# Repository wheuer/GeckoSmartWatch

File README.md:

# Gecko Smart Watch

This repository tracks the most recent state of my personal smart watch project.

It's a mess and unpolished. For a more in depth look at the project and it's history see [my website](https://www.williamfheuer.com/project-portfolio).

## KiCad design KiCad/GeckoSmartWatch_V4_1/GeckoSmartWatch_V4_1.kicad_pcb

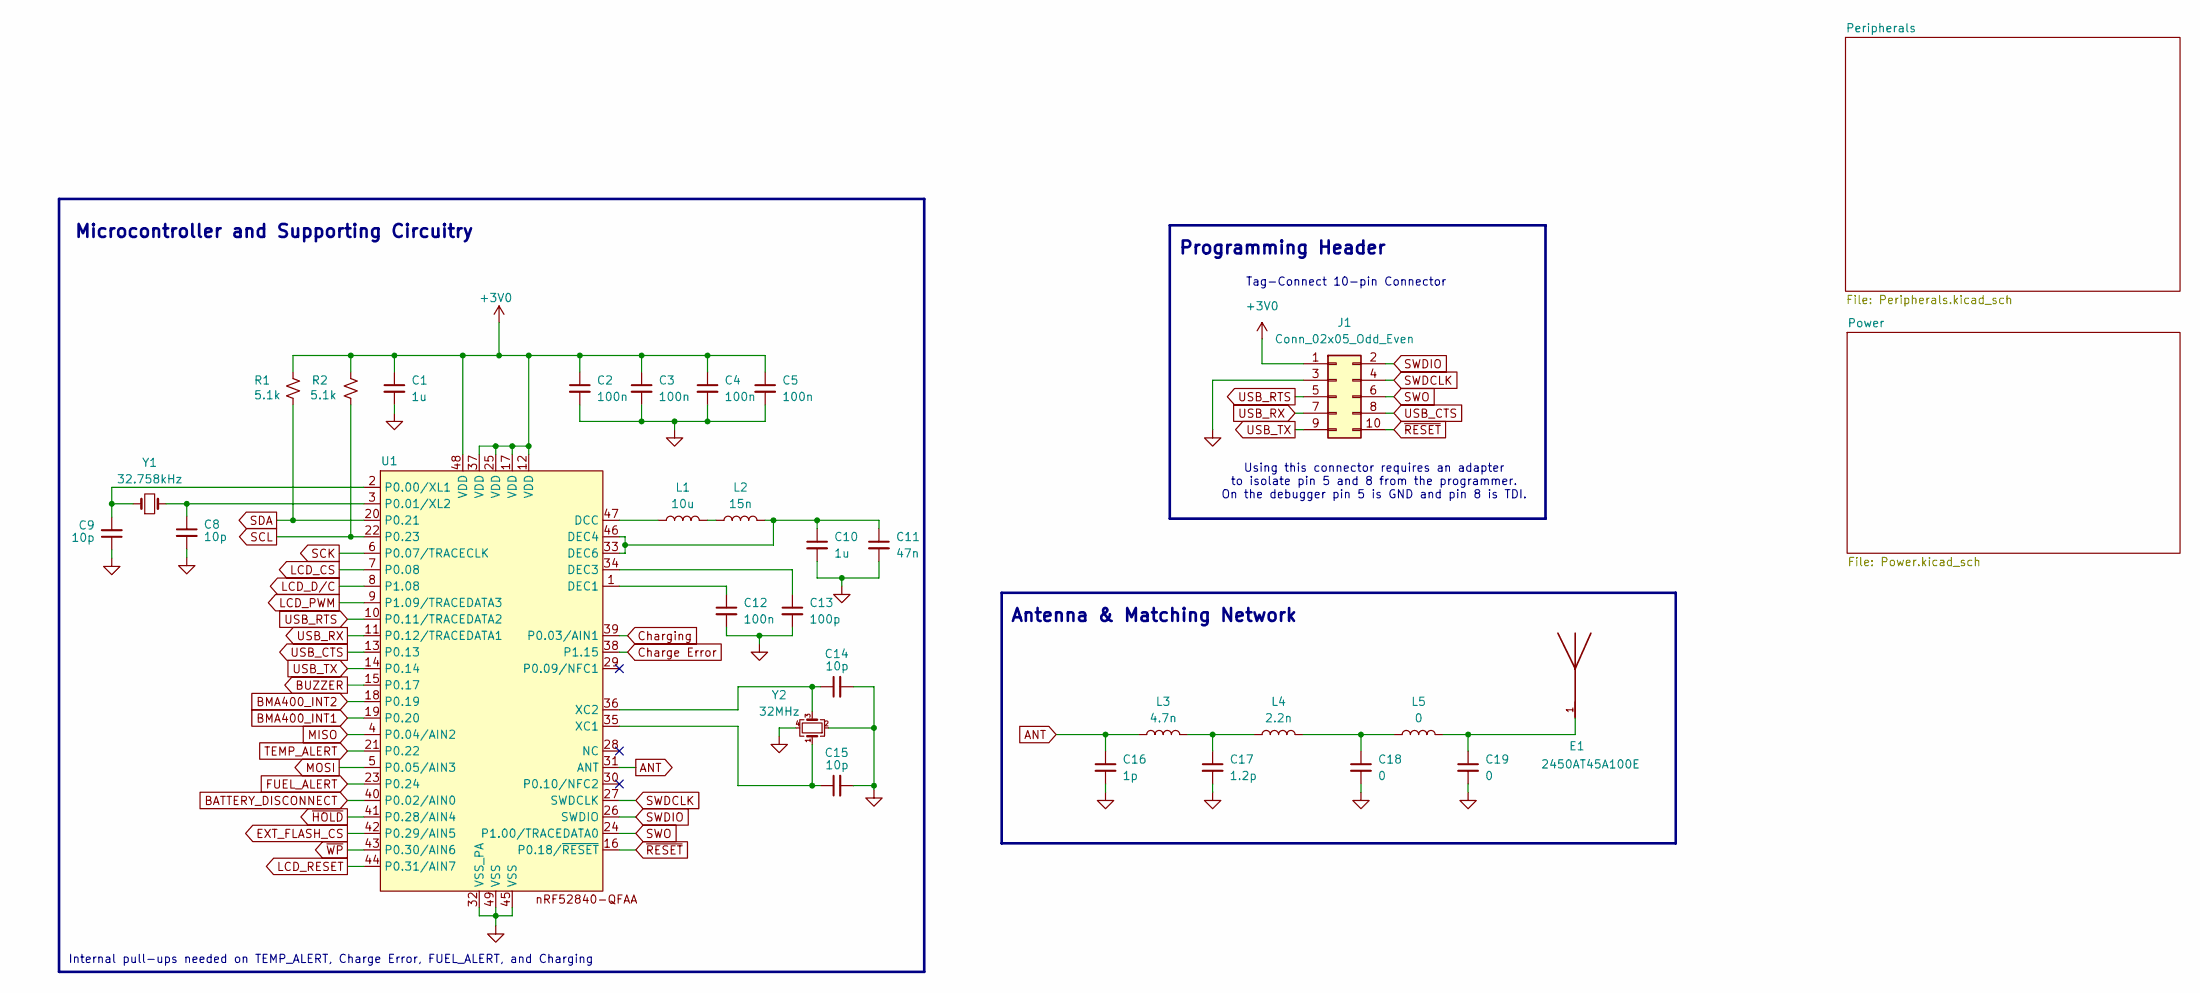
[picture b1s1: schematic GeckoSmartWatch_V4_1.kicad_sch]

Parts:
C1, C10: 1u; C_0402_1005Metric
C2, C3, C4, C5, C12: 100n; C_0402_1005Metric
C8, C9, C14, C15: 10p; C_0402_1005Metric
C11: 47n; C_0402_1005Metric
C13: 100p; C_0402_1005Metric
C16: 1p; C_0402_1005Metric
C17: 1.2p; C_0402_1005Metric
C18, C19: 0; C_0402_1005Metric
E1: 2450AT45A100E; ANT_2450AT45A100E; PARTREV 3.1
J1: Conn_02x05_Odd_Even; TAG-CONNECT_TC2050-IDC-NL
L1: 10u; L_0603_1608Metric
L2: 15n; L_0402_1005Metric
L3: 4.7n; L_0402_1005Metric
L4: 2.2n; L_0402_1005Metric
L5: 0; L_0402_1005Metric
R1, R2: 5.1k; R_0402_1005Metric
U1: nrf52840_QFN40P600X600X95-49N-D
Y1: 32.758kHz; 32kHz_ECS32712512RCTR
Y2: 32MHz; 32MHz_ECS320837CKMTR3

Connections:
+3V0: C1.1, C2.1, C3.1, C4.1, C5.1, J1.1, R1.2, R2.2, U1.12 (VDD), U1.17 (VDD), U1.25 (VDD), U1.37 (VDD), U1.48 (VDD); also elsewhere on the board
ANT: C16.1, L3.1, U1.31 (ANT)
BATTERY_DISCONNECT: U1.40 (P0.02/AIN0); also elsewhere on the board
BMA400_INT1: U1.19 (P0.20); also elsewhere on the board
BMA400_INT2: U1.18 (P0.19); also elsewhere on the board
BUZZER: U1.15 (P0.17); also elsewhere on the board
Charge Error: U1.38 (P1.15); also elsewhere on the board
Charging: U1.39 (P0.03/AIN1); also elsewhere on the board
EXT_FLASH_CS: U1.42 (P0.29/AIN5); also elsewhere on the board
FUEL_ALERT: U1.23 (P0.24); also elsewhere on the board
GND: C1.2, C2.2, C3.2, C4.2, C5.2, C8.2, C9.1, C10.2, C11.2, C12.2, C13.2, C14.2, C15.2, C16.2, C17.2, C18.2, C19.2, J1.3, U1.32 (VSS_PA), U1.45 (VSS), U1.49 (VSS), Y2.2, Y2.4; also elsewhere on the board
LCD_CS: U1.7 (P0.08); also elsewhere on the board
LCD_D/C: U1.8 (P1.08); also elsewhere on the board
LCD_PWM: U1.9 (P1.09/TRACEDATA3); also elsewhere on the board
LCD_RESET: U1.44 (P0.31/AIN7); also elsewhere on the board
MISO: U1.4 (P0.04/AIN2); also elsewhere on the board
MOSI: U1.5 (P0.05/AIN3); also elsewhere on the board
unnamed: C17.1, L3.2, L4.1
unnamed: C18.1, L4.2, L5.1
unnamed: C19.1, E1.1, L5.2
unnamed: L1.2, L2.1
unnamed: L1.1, U1.47 (DCC)
unnamed: C12.1, U1.1 (DEC1)
unnamed: C13.1, U1.34 (DEC3)
unnamed: C10.1, C11.1, L2.2, U1.33 (DEC6), U1.46 (DEC4)
unnamed: C9.2, U1.2 (P0.00/XL1), Y1.1
unnamed: C8.1, U1.3 (P0.01/XL2), Y1.2
unnamed: C15.1, U1.35 (XC1), Y2.1
unnamed: C14.1, U1.36 (XC2), Y2.3
SCK: U1.6 (P0.07/TRACECLK); also elsewhere on the board
SCL: R2.1, U1.22 (P0.23); also elsewhere on the board
SDA: R1.1, U1.20 (P0.21); also elsewhere on the board
SWDCLK: J1.4, U1.27 (SWDCLK)
SWDIO: J1.2, U1.26 (SWDIO)
SWO: J1.6, U1.24 (P1.00/TRACEDATA0)
TEMP_ALERT: U1.21 (P0.22); also elsewhere on the board
USB_CTS: J1.8, U1.13 (P0.13)
USB_RTS: J1.5, U1.10 (P0.11/TRACEDATA2)
USB_RX: J1.7, U1.11 (P0.12/TRACEDATA1)
USB_TX: J1.9, U1.14 (P0.14)
~HOLD: U1.41 (P0.28/AIN4); also elsewhere on the board
~RESET: J1.10, U1.16 (P0.18/~RESET)
~WP: U1.43 (P0.30/AIN6); also elsewhere on the board

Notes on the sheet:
Antenna & Matching Network
Using this connector requires an adapter to isolate pin 5 and 8 from the programmer. On the debugger pin 5 is GND and pin 8 is TDI.
Internal pull-ups needed on TEMP_ALERT, Charge Error, FUEL_ALERT, and Charging
Tag-Connect 10-pin Connector
Programming Header
Microcontroller and Supporting Circuitry

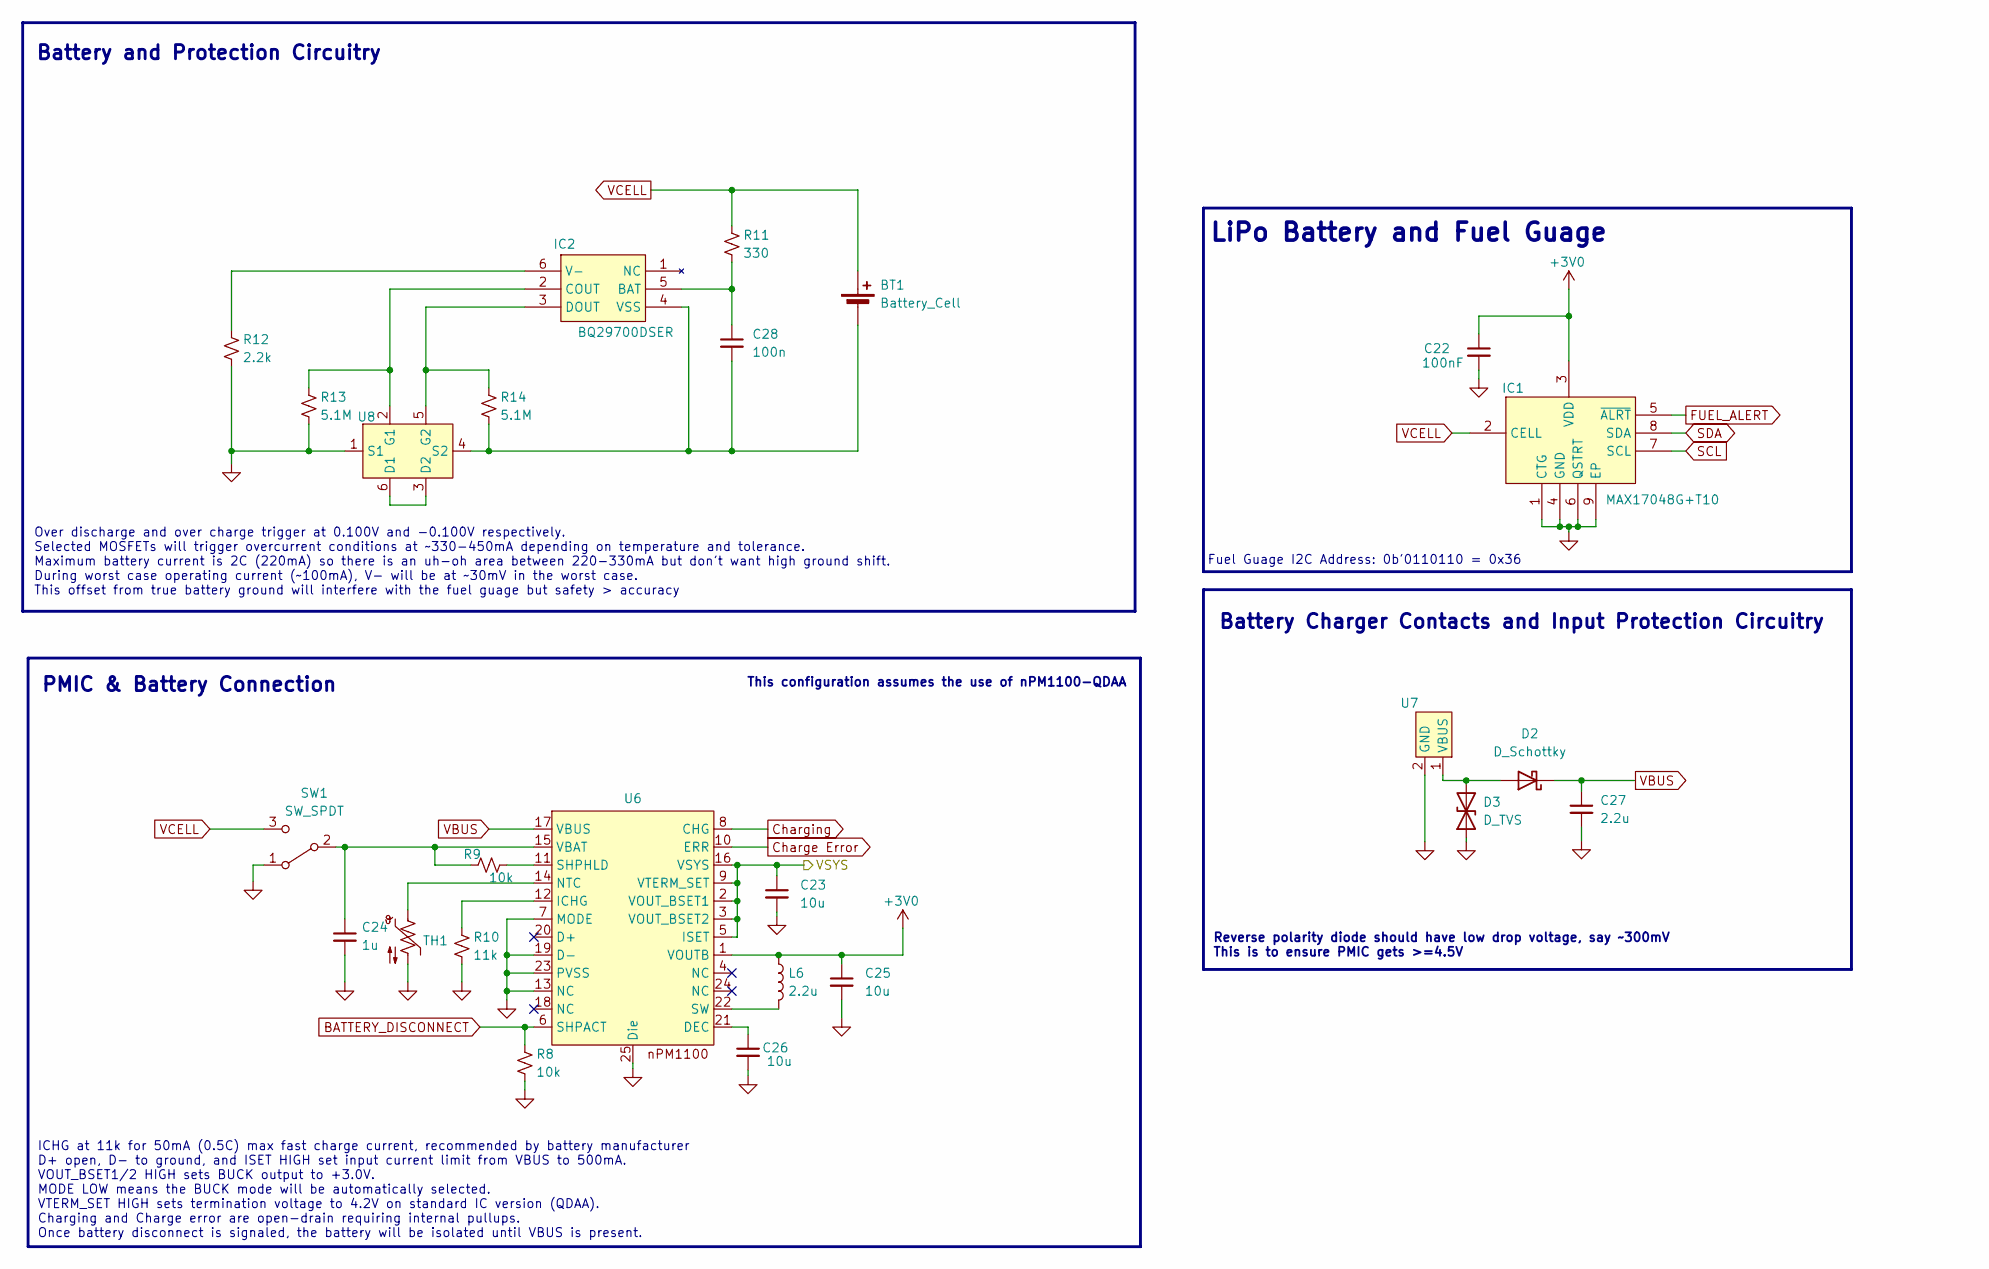
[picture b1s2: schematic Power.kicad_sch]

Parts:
BT1: Battery_Cell; RJD2430C1ST1
C22: 100nF; C_0402_1005Metric
C23, C25, C26: 10u; C_0402_1005Metric
C24: 1u; C_0402_1005Metric
C27: 2.2u; C_0402_1005Metric
C28: 100n; C_0402_1005Metric
D2: D_Schottky; reversePolarity_SODFL3616X98N
D3: D_TVS; TVS_SOD2513X120N
IC1: MAX17048G+T10; MAX17048_fuelGuague; Mouser Part Number 700-MAX17048G+T10
IC2: BQ29700DSER; batProtect_SON50P150X150X80-6N; Mouser Part Number 595-BQ29700DSER
L6: 2.2u; L_0402_1005Metric
R8, R9: 10k; R_0402_1005Metric
R10: 11k; R_0402_1005Metric
R11: 330; R_0402_1005Metric
R12: 2.2k; R_0402_1005Metric
R13, R14: 5.1M; R_0402_1005Metric
SW1: SW_SPDT; pwrSW_B-TYPE
TH1: Thermistor_NTC_US; R_0402_1005Metric
U6: nPM1100_QFN50P400X400X90-25N-D
U7: chargeContacts_RHDR2W51P0X254_1X2_508X254X419P
U8: batMOS_SOTFL95P280X88-6N

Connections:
+3V0: C22.1, C25.1, IC1.3 (VDD), L6.1, U6.1 (VOUTB); also elsewhere on the board
/Power/VSYS: C23.1, U6.2 (VOUT_BSET1), U6.3 (VOUT_BSET2), U6.5 (ISET), U6.9 (VTERM_SET), U6.16 (VSYS)
BATTERY_DISCONNECT: R8.1, U6.6 (SHPACT); also elsewhere on the board
Charge Error: U6.10 (ERR); also elsewhere on the board
Charging: U6.8 (CHG); also elsewhere on the board
FUEL_ALERT: IC1.5 (~ALRT); also elsewhere on the board
GND: C22.2, C23.2, C24.2, C25.2, C26.2, C27.2, D3.1 (A1), IC1.1 (CTG), IC1.4 (GND), IC1.6 (QSTRT), IC1.9 (EP), R8.2, R10.2, R12.2, R13.2, SW1.1 (A), TH1.2, U6.7 (MODE), U6.13 (NC), U6.19 (D-), U6.23 (PVSS), U6.25 (Die), U7.2 (GND), U8.1 (S1); also elsewhere on the board
unnamed: BT1.2 (-), C28.2, IC2.4 (VSS), R14.2, U8.4 (S2)
unnamed: D2.2 (A), D3.2 (A2), U7.1 (VBUS)
unnamed: C28.1, IC2.5 (BAT), R11.2
unnamed: IC2.2 (COUT), R13.1, U8.2 (G1)
unnamed: IC2.3 (DOUT), R14.1, U8.5 (G2)
unnamed: IC2.6 (V-), R12.1
unnamed: C24.1, R9.1, SW1.2 (B), U6.15 (VBAT)
unnamed: C26.1, U6.21 (DEC)
unnamed: R10.1, U6.12 (ICHG)
unnamed: TH1.1, U6.14 (NTC)
unnamed: R9.2, U6.11 (SHPHLD)
unnamed: L6.2, U6.22 (SW)
unnamed: U8.3 (D2), U8.6 (D1)
SCL: IC1.7 (SCL); also elsewhere on the board
SDA: IC1.8 (SDA); also elsewhere on the board
VBUS: C27.1, D2.1 (K), U6.17 (VBUS)
VCELL: BT1.1 (+), IC1.2 (CELL), R11.1, SW1.3 (C)

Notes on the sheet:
Battery and Protection Circuitry
Reverse polarity diode should have low drop voltage, say ~300mV This is to ensure PMIC gets >=4.5V
Over discharge and over charge trigger at 0.100V and -0.100V respectively. Selected MOSFETs will trigger overcurrent conditions at ~330-450mA depending on temperature and tolerance. Maximum battery current is 2C (220mA) so there is an uh-oh area between 220-330mA but don't want high ground shift. D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
This configuration assumes the use of nPM1100-QDAA
Battery Charger Contacts and Input Protection Circuitry
LiPo Battery and Fuel Guage
Fuel Guage I2C Address: 0b'0110110 = 0x36
PMIC & Battery Connection
ICHG at 11k for 50mA (0.5C) max fast charge current, recommended by battery manufacturer D+ open, D- to ground, and ISET HIGH set input current limit from VBUS to 500mA. VOUT_BSET1/2 HIGH sets BUCK output to +3.0V. MODE LOW means the BUCK mode will be automatically selected. VTERM_SET HIGH sets ter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

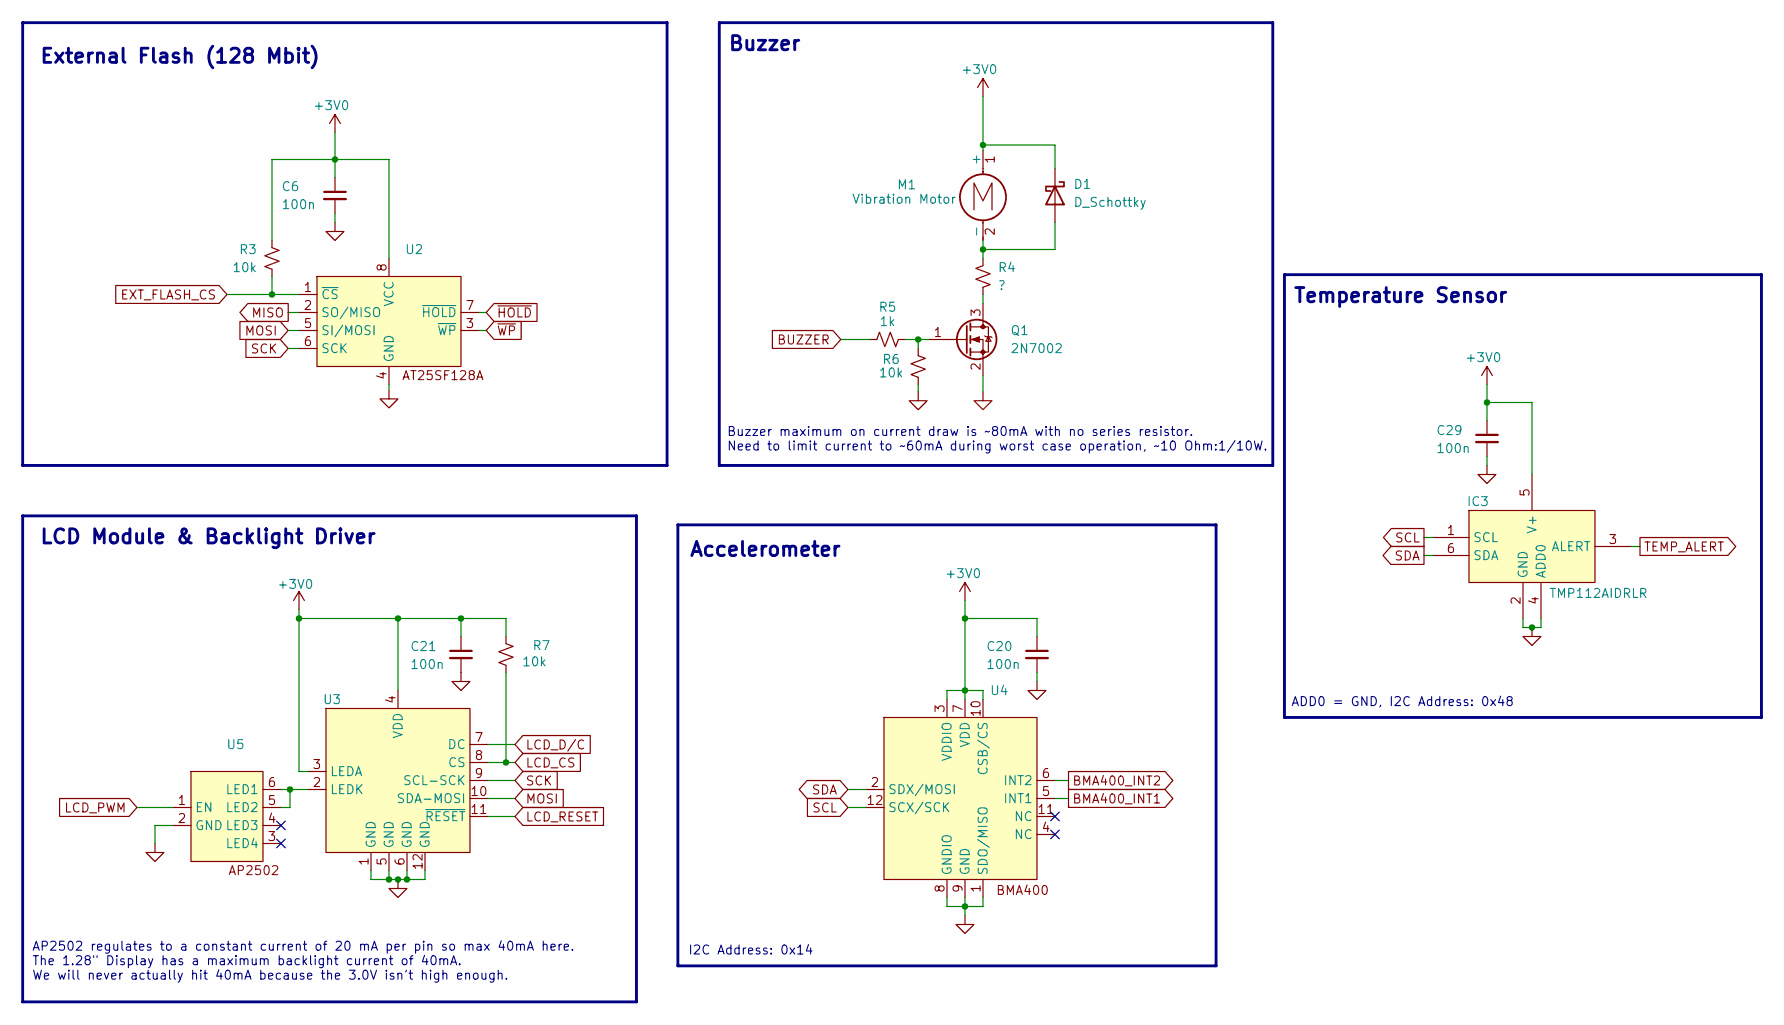
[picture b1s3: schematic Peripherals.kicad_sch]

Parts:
C6, C20, C21, C29: 100n; C_0402_1005Metric
D1: D_Schottky; flyback_SODFL1608X70N
IC3: TMP112AIDRLR; tmp_SOTFL50P160X60-6N; Mouser Part Number 595-TMP112AIDRLR
M1: Vibration Motor; SMD_vibrationMotor
Q1: 2N7002; SOT-23
R3, R6, R7: 10k; R_0402_1005Metric
R4: ?; R_0402_1005Metric
R5: 1k; R_0402_1005Metric
U2: extFlash_SON127P600X500X60-9N-D
U3: 1.47_TFT_displayConnector
U4: BOSCH_LGA_12
U5: AP2502_SOT95P280X145-6N

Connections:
+3V0: C6.1, C20.1, C21.1, C29.1, D1.1 (K), IC3.5 (V+), M1.1 (+), R3.1, R7.1, U2.8 (VCC), U3.3 (LEDA), U3.4 (VDD), U4.3 (VDDIO), U4.7 (VDD), U4.10 (CSB/CS); also elsewhere on the board
BMA400_INT1: U4.5 (INT1); also elsewhere on the board
BMA400_INT2: U4.6 (INT2); also elsewhere on the board
BUZZER: R5.1; also elsewhere on the board
EXT_FLASH_CS: R3.2, U2.1 (~CS); also elsewhere on the board
GND: C6.2, C20.2, C21.2, C29.2, IC3.2 (GND), IC3.4 (ADD0), Q1.2 (S), R6.1, U2.4 (GND), U3.1 (GND), U3.5 (GND), U3.6 (GND), U3.12 (GND), U4.1 (SDO/MISO), U4.8 (GNDIO), U4.9 (GND), U5.2 (GND); also elsewhere on the board
LCD_CS: R7.2, U3.8 (CS); also elsewhere on the board
LCD_D/C: U3.7 (DC); also elsewhere on the board
LCD_PWM: U5.1 (EN); also elsewhere on the board
LCD_RESET: U3.11 (~RESET); also elsewhere on the board
MISO: U2.2 (SO/MISO); also elsewhere on the board
MOSI: U2.5 (SI/MOSI), U3.10 (SDA-MOSI); also elsewhere on the board
unnamed: D1.2 (A), M1.2 (-), R4.1
unnamed: Q1.3 (D), R4.2
unnamed: Q1.1 (G), R5.2, R6.2
unnamed: U3.2 (LEDK), U5.5 (LED2), U5.6 (LED1)
SCK: U2.6 (SCK), U3.9 (SCL-SCK); also elsewhere on the board
SCL: IC3.1 (SCL), U4.12 (SCX/SCK); also elsewhere on the board
SDA: IC3.6 (SDA), U4.2 (SDX/MOSI); also elsewhere on the board
TEMP_ALERT: IC3.3 (ALERT); also elsewhere on the board
~HOLD: U2.7 (~HOLD); also elsewhere on the board
~WP: U2.3 (~WP); also elsewhere on the board

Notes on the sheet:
Buzzer
I2C Address: 0x14
ADD0 = GND, I2C Address: 0x48
AP2502 regulates to a constant current of 20 mA per pin so max 40mA here. The 1.28" Display has a maximum backlight current of 40mA. We will never actually hit 40mA because the 3.0V isn't high enough.
Buzzer maximum on current draw is ~80mA with no series resistor. Need to limit current to ~60mA during worst case operation, ~10 Ohm:1/10W.
Temperature Sensor
External Flash (128 Mbit)
LCD Module & Backlight Driver
Accelerometer

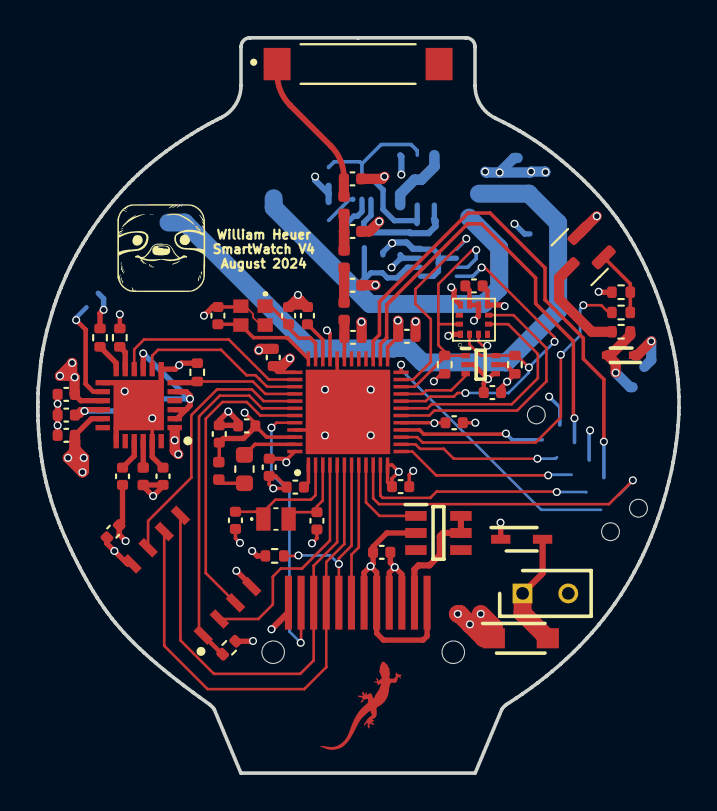
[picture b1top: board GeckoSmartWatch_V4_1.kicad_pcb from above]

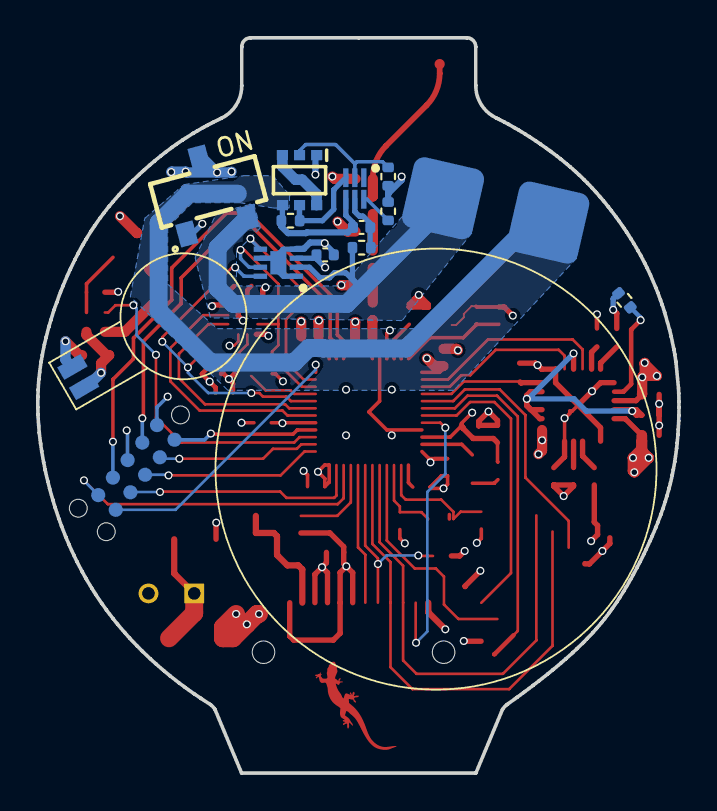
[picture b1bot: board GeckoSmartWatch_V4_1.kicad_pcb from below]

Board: 4 copper layers, 35.6 x 40.9 mm, 71 parts (14 on the bottom side), 63 nets.

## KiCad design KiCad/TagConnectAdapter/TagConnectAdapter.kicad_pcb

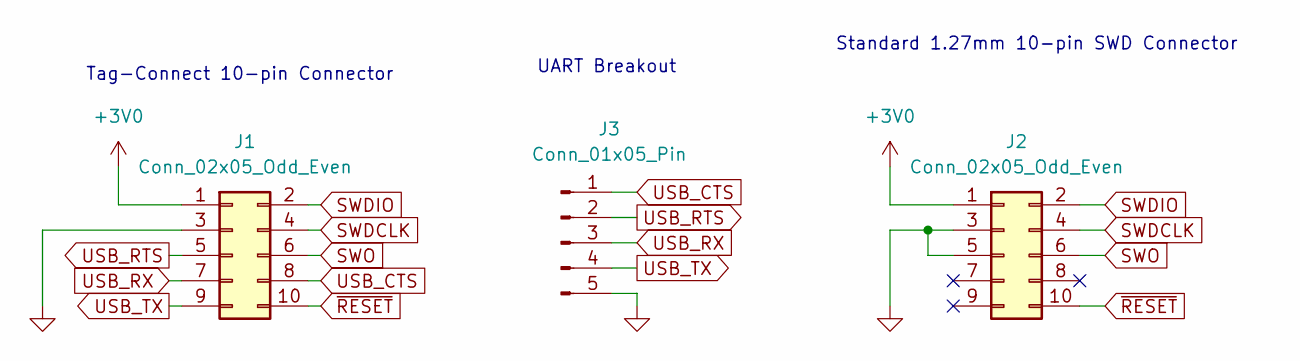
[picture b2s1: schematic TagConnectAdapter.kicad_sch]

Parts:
J1: Conn_02x05_Odd_Even; CNC_TECH_1.27mm_10-pin
J2: Conn_02x05_Odd_Even; AMPHENOL_20021311-00010T4LF
J3: Conn_01x05_Pin; PinSocket_1x05_P2.54mm_Vertical

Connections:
+3V0: J1.1, J2.1
GND: J1.3, J2.3, J2.5, J3.5
SWDCLK: J1.4, J2.4
SWDIO: J1.2, J2.2
SWO: J1.6, J2.6
USB_CTS: J1.8, J3.1
USB_RTS: J1.5, J3.2
USB_RX: J1.7, J3.3
USB_TX: J1.9, J3.4
~RESET: J1.10, J2.10

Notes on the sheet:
Standard 1.27mm 10-pin SWD Connector
UART Breakout
Tag-Connect 10-pin Connector

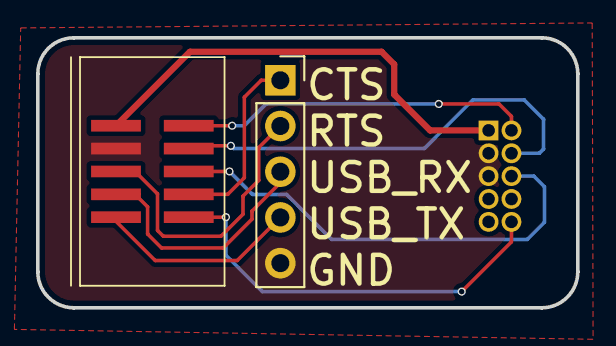
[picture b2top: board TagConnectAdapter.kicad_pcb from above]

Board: 2 copper layers, 30.0 x 15.0 mm, 3 parts (1 on the bottom side), 10 nets.

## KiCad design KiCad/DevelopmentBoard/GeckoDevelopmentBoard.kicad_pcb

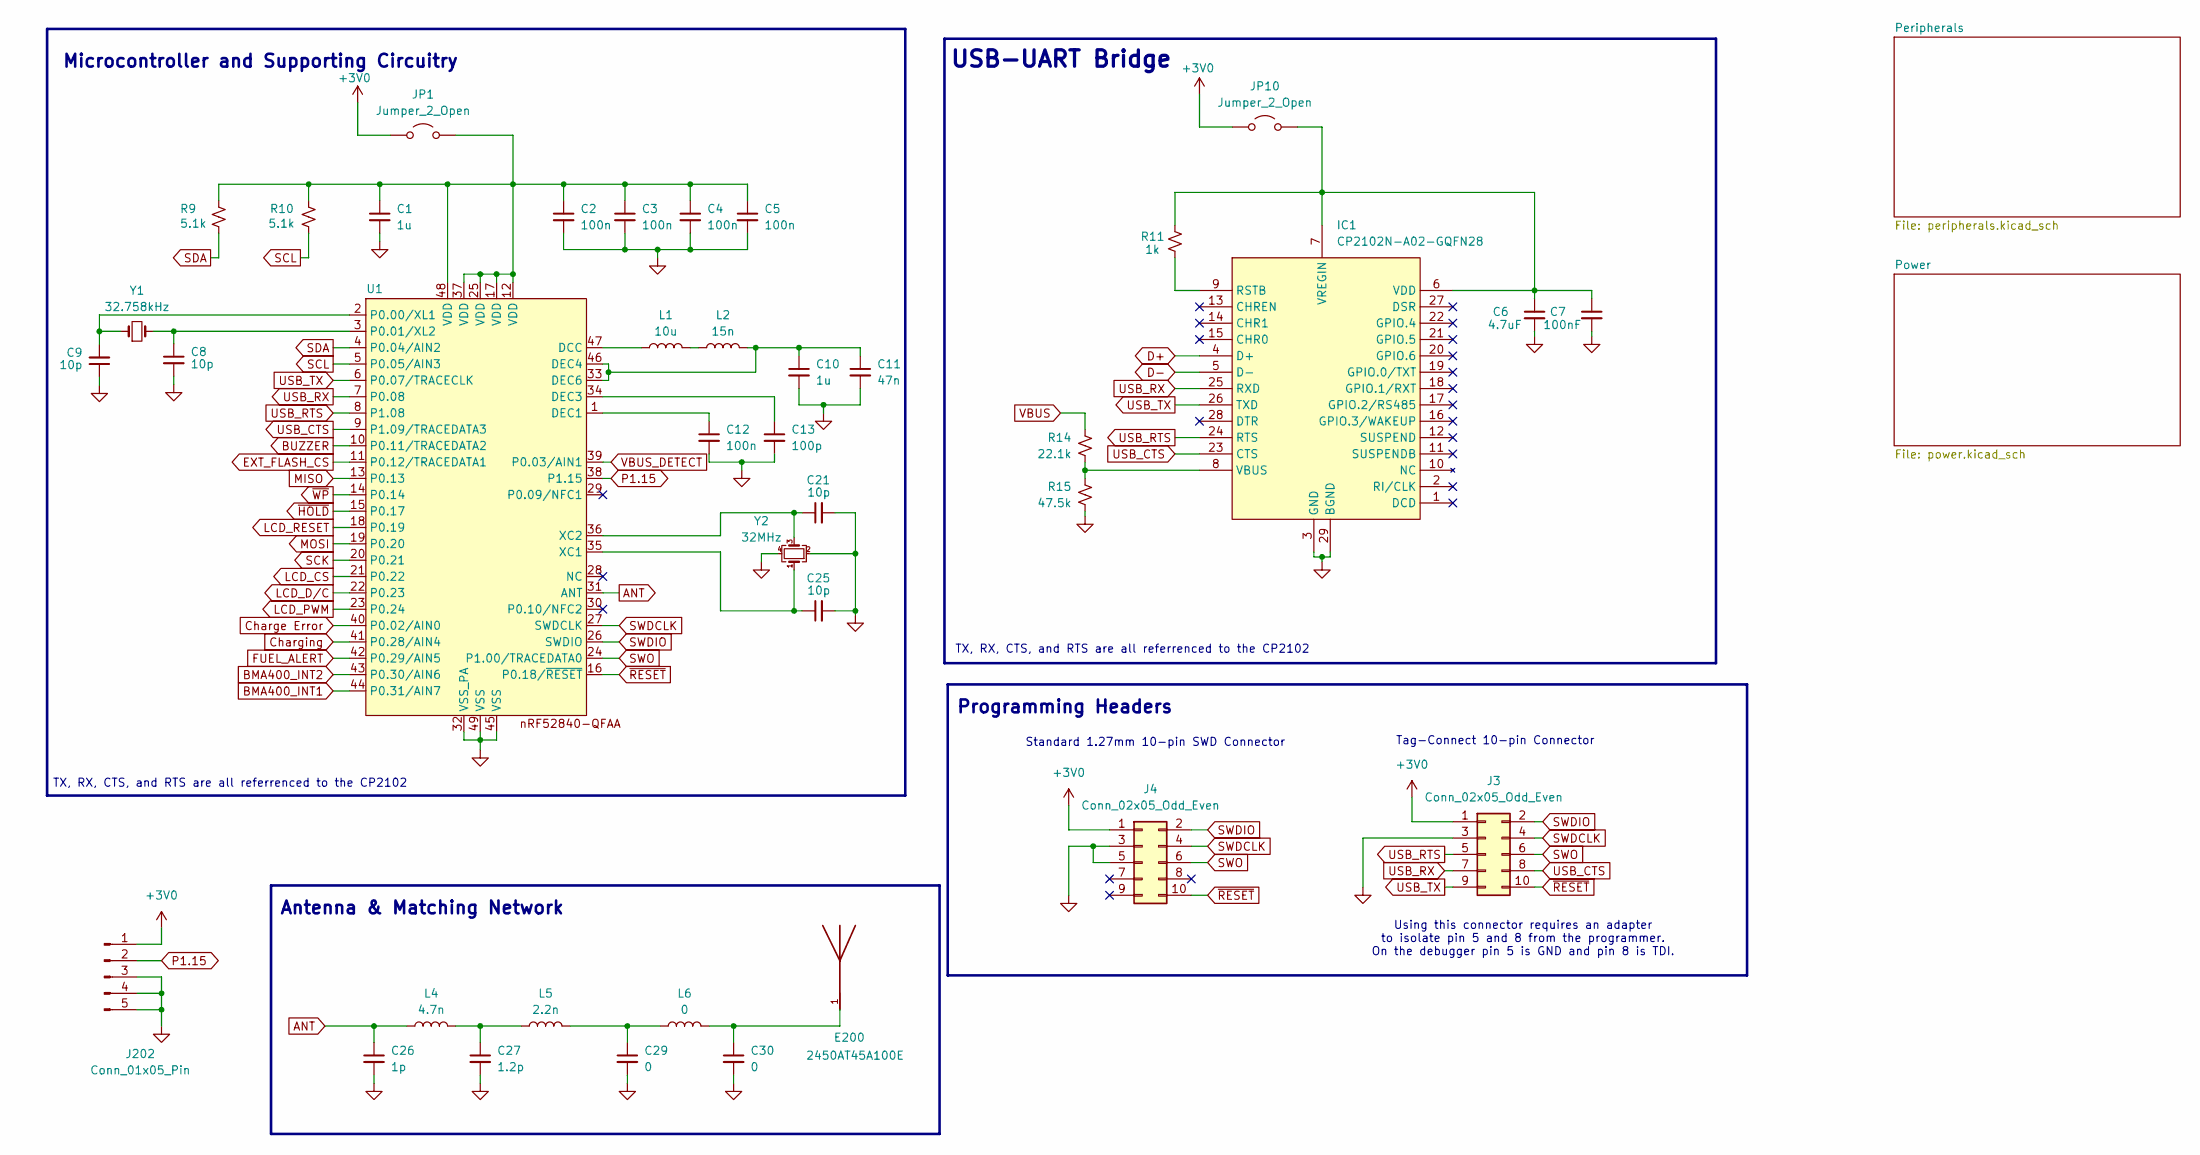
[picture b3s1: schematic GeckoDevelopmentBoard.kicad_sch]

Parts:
C1, C10: 1u; C_0402_1005Metric
C2, C3, C4, C5, C12: 100n; C_0402_1005Metric
C6: 4.7uF; C_0402_1005Metric
C7: 100nF; C_0402_1005Metric
C8, C9, C21, C25: 10p; C_0402_1005Metric
C11: 47n; C_0402_1005Metric
C13: 100p; C_0402_1005Metric
C26: 1p; C_0402_1005Metric
C27: 1.2p; C_0402_1005Metric
C29, C30: 0; C_0402_1005Metric
E200: 2450AT45A100E; ANT_2450AT45A100E; PARTREV 3.1
IC1: CP2102N-A02-GQFN28; CP2102_5x5QFN; Mouser Part Number 634-CP2102NA02GQFN28
J3: Conn_02x05_Odd_Even; TAG-CONNECT_TC2050-IDC-NL
J4: Conn_02x05_Odd_Even; CNC_TECH_1.27mm_10-pin
J202: Conn_01x05_Pin; PinHeader_1x05_P2.54mm_Vertical
JP1, JP10: Jumper_2_Open; 2pinJumper_HDRV2W110P0X254_1X2_508X254X854P
L1: 10u; L_0603_1608Metric
L2: 15n; L_0402_1005Metric
L4: 4.7n; L_0402_1005Metric
L5: 2.2n; L_0402_1005Metric
L6: 0; L_0402_1005Metric
R9, R10: 5.1k; R_0402_1005Metric
R11: 1k; R_0402_1005Metric
R14: 22.1k; R_0402_1005Metric
R15: 47.5k; R_0402_1005Metric
U1: nrf52840_QFN40P600X600X95-49N-D
Y1: 32.758kHz; 32kHz_ECS32712512RCTR
Y2: 32MHz; 32MHz_ECS320837CKMTR3

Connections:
+3V0: J3.1, J4.1, J202.1, JP1.1 (A), JP10.1 (A); also elsewhere on the board
ANT: C26.1, L4.1, U1.31 (ANT)
BMA400_INT1: U1.44 (P0.31/AIN7); also elsewhere on the board
BMA400_INT2: U1.43 (P0.30/AIN6); also elsewhere on the board
BUZZER: U1.10 (P0.11/TRACEDATA2); also elsewhere on the board
Charge Error: U1.40 (P0.02/AIN0); also elsewhere on the board
Charging: U1.41 (P0.28/AIN4); also elsewhere on the board
D+: IC1.4 (D+); also elsewhere on the board
D-: IC1.5 (D-); also elsewhere on the board
EXT_FLASH_CS: U1.11 (P0.12/TRACEDATA1); also elsewhere on the board
FUEL_ALERT: U1.42 (P0.29/AIN5); also elsewhere on the board
GND: C1.2, C2.2, C3.2, C4.2, C5.2, C6.2, C7.2, C8.2, C9.1, C10.2, C11.2, C12.2, C13.2, C21.2, C25.2, C26.2, C27.2, C29.2, C30.2, IC1.3 (GND), IC1.29 (BGND), J3.3, J4.3, J4.5, J202.3, J202.4, J202.5, R15.2, U1.32 (VSS_PA), U1.45 (VSS), U1.49 (VSS), Y2.2, Y2.4; also elsewhere on the board
LCD_CS: U1.21 (P0.22); also elsewhere on the board
LCD_D/C: U1.22 (P0.23); also elsewhere on the board
LCD_PWM: U1.23 (P0.24); also elsewhere on the board
LCD_RESET: U1.18 (P0.19); also elsewhere on the board
MISO: U1.13 (P0.13); also elsewhere on the board
MOSI: U1.19 (P0.20); also elsewhere on the board
unnamed: C27.1, L4.2, L5.1
unnamed: C29.1, L5.2, L6.1
unnamed: C30.1, E200.1, L6.2
unnamed: IC1.9 (RSTB), R11.2
unnamed: IC1.8 (VBUS), R14.2, R15.1
unnamed: C6.1, C7.1, IC1.6 (VDD), IC1.7 (VREGIN), JP10.2 (B), R11.1
unnamed: C1.1, C2.1, C3.1, C4.1, C5.1, JP1.2 (B), R9.2, R10.2, U1.12 (VDD), U1.17 (VDD), U1.25 (VDD), U1.37 (VDD), U1.48 (VDD)
unnamed: L1.2, L2.1
unnamed: L1.1, U1.47 (DCC)
unnamed: C12.1, U1.1 (DEC1)
unnamed: C13.1, U1.34 (DEC3)
unnamed: C10.1, C11.1, L2.2, U1.33 (DEC6), U1.46 (DEC4)
unnamed: C9.2, U1.2 (P0.00/XL1), Y1.1
unnamed: C8.1, U1.3 (P0.01/XL2), Y1.2
unnamed: C25.1, U1.35 (XC1), Y2.1
unnamed: C21.1, U1.36 (XC2), Y2.3
P1.15: J202.2, U1.38 (P1.15)
SCK: U1.20 (P0.21); also elsewhere on the board
SCL: R10.1, U1.5 (P0.05/AIN3); also elsewhere on the board
SDA: R9.1, U1.4 (P0.04/AIN2); also elsewhere on the board
SWDCLK: J3.4, J4.4, U1.27 (SWDCLK)
SWDIO: J3.2, J4.2, U1.26 (SWDIO)
SWO: J3.6, J4.6, U1.24 (P1.00/TRACEDATA0)
USB_CTS: IC1.23 (CTS), J3.8, U1.9 (P1.09/TRACEDATA3)
USB_RTS: IC1.24 (RTS), J3.5, U1.8 (P1.08)
USB_RX: IC1.25 (RXD), J3.7, U1.7 (P0.08)
USB_TX: IC1.26 (TXD), J3.9, U1.6 (P0.07/TRACECLK)
VBUS: R14.1; also elsewhere on the board
VBUS_DETECT: U1.39 (P0.03/AIN1); also elsewhere on the board
~HOLD: U1.15 (P0.17); also elsewhere on the board
~RESET: J3.10, J4.10, U1.16 (P0.18/~RESET)
~WP: U1.14 (P0.14); also elsewhere on the board

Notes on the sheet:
USB-UART Bridge
TX, RX, CTS, and RTS are all referrenced to the CP2102
Tag-Connect 10-pin Connector
Antenna & Matching Network
Programming Headers
Standard 1.27mm 10-pin SWD Connector
Microcontroller and Supporting Circuitry
Using this connector requires an adapter to isolate pin 5 and 8 from the programmer. On the debugger pin 5 is GND and pin 8 is TDI.

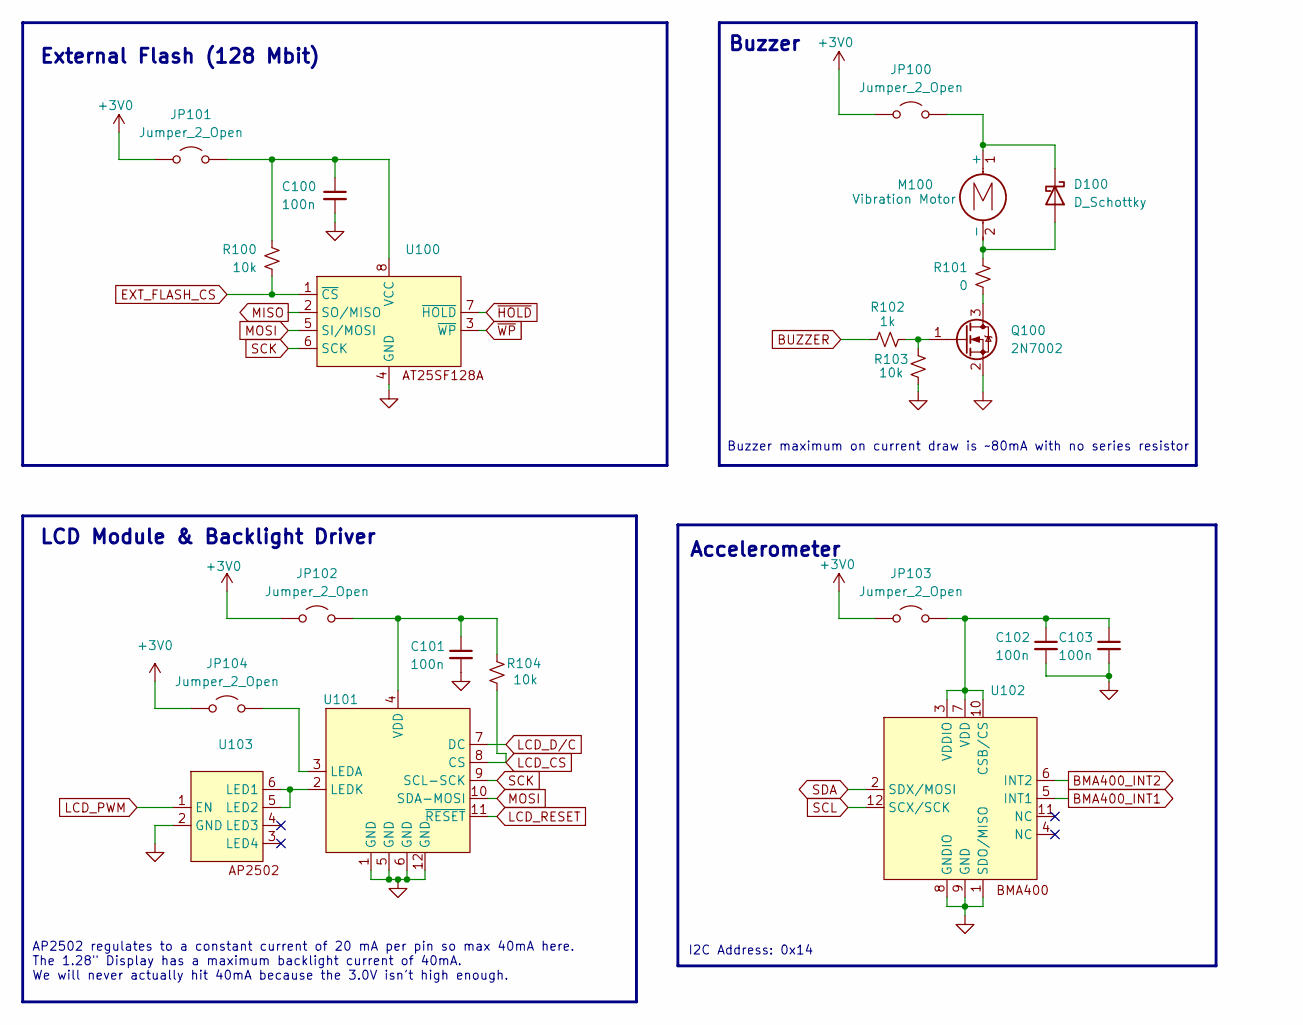
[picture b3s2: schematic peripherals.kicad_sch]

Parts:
C100, C101, C102, C103: 100n; C_0402_1005Metric
D100: D_Schottky; flyback_SODFL1608X70N
JP100, JP101, JP102, JP103, JP104: Jumper_2_Open; 2pinJumper_HDRV2W110P0X254_1X2_508X254X854P
M100: Vibration Motor; SMD_vibrationMotor
Q100: 2N7002; SOT-23
R100, R103, R104: 10k; R_0402_1005Metric
R101: 0; R_0603_1608Metric
R102: 1k; R_0402_1005Metric
U100: extFlash_SON127P600X500X60-9N-D
U101: 1.47_TFT_displayConnector
U102: BOSCH_LGA_12
U103: AP2502_SOT95P280X145-6N

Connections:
+3V0: JP100.1 (A), JP101.1 (A), JP102.1 (A), JP103.1 (A), JP104.1 (A); also elsewhere on the board
BMA400_INT1: U102.5 (INT1); also elsewhere on the board
BMA400_INT2: U102.6 (INT2); also elsewhere on the board
BUZZER: R102.1; also elsewhere on the board
EXT_FLASH_CS: R100.2, U100.1 (~CS); also elsewhere on the board
GND: C100.2, C101.2, C102.2, C103.2, Q100.2 (S), R103.1, U100.4 (GND), U101.1 (GND), U101.5 (GND), U101.6 (GND), U101.12 (GND), U102.1 (SDO/MISO), U102.8 (GNDIO), U102.9 (GND), U103.2 (GND); also elsewhere on the board
LCD_CS: R104.2, U101.8 (CS); also elsewhere on the board
LCD_D/C: U101.7 (DC); also elsewhere on the board
LCD_PWM: U103.1 (EN); also elsewhere on the board
LCD_RESET: U101.11 (~RESET); also elsewhere on the board
MISO: U100.2 (SO/MISO); also elsewhere on the board
MOSI: U100.5 (SI/MOSI), U101.10 (SDA-MOSI); also elsewhere on the board
unnamed: D100.2 (A), M100.2 (-), R101.1
unnamed: D100.1 (K), JP100.2 (B), M100.1 (+)
unnamed: C100.1, JP101.2 (B), R100.1, U100.8 (VCC)
unnamed: C101.1, JP102.2 (B), R104.1, U101.4 (VDD)
unnamed: C102.1, C103.1, JP103.2 (B), U102.3 (VDDIO), U102.7 (VDD), U102.10 (CSB/CS)
unnamed: JP104.2 (B), U101.3 (LEDA)
unnamed: Q100.3 (D), R101.2
unnamed: Q100.1 (G), R102.2, R103.2
unnamed: U101.2 (LEDK), U103.5 (LED2), U103.6 (LED1)
SCK: U100.6 (SCK), U101.9 (SCL-SCK); also elsewhere on the board
SCL: U102.12 (SCX/SCK); also elsewhere on the board
SDA: U102.2 (SDX/MOSI); also elsewhere on the board
~HOLD: U100.7 (~HOLD); also elsewhere on the board
~WP: U100.3 (~WP); also elsewhere on the board

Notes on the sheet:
AP2502 regulates to a constant current of 20 mA per pin so max 40mA here. The 1.28" Display has a maximum backlight current of 40mA. We will never actually hit 40mA because the 3.0V isn't high enough.
LCD Module & Backlight Driver
Buzzer
Accelerometer
Buzzer maximum on current draw is ~80mA with no series resistor
External Flash (128 Mbit)
I2C Address: 0x14
